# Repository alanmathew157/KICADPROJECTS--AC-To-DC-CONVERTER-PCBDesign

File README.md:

# AC to DC Converter PCB Design using KICAD -ALTIMUM
## PCB TOP VIEW

## PCB BOTTOM VIEW

## Project Overview
This project is an AC to DC converter circuit designed to convert alternating current (AC) input into a stable direct current (DC) output. The circuit uses a transformer to step down the input voltage, a bridge rectifier to convert AC to pulsating DC, and a filter capacitor to smooth the output. It demonstrates the basic principles of power supply design and provides a reliable DC source suitable for low-voltage electronic applications. This is my first KiCad project, created to learn schematic design and understand the fundamentals of circuit development

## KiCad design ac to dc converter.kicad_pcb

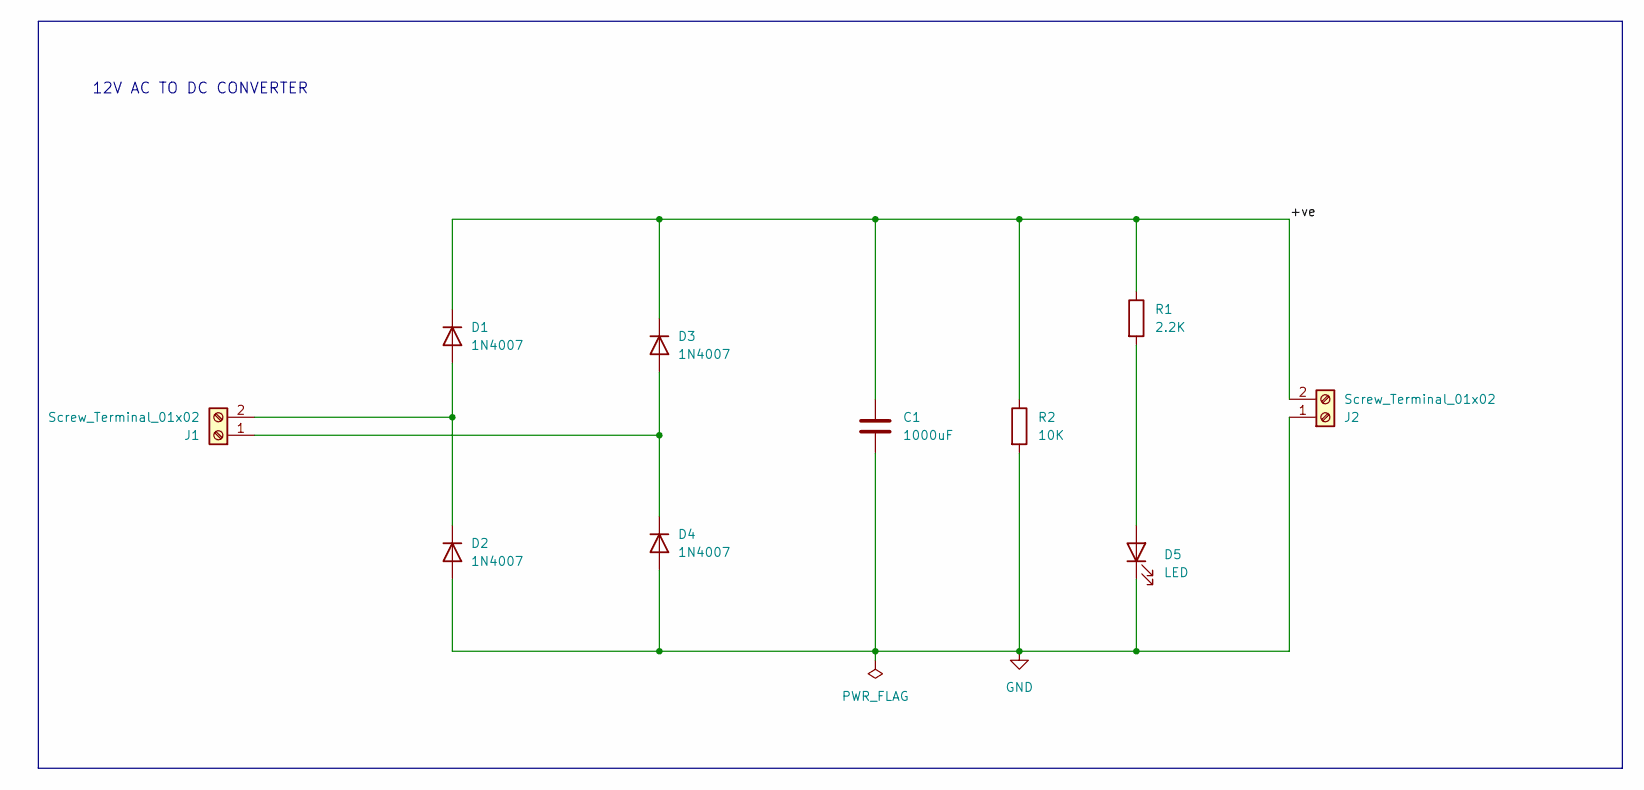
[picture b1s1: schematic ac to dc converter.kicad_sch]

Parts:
C1: 1000uF; C_Radial_D8.0mm_H11.5mm_P3.50mm
D1, D2, D3, D4: 1N4007; D_DO-41_SOD81_P10.16mm_Horizontal
D5: LED; LED_D5.0mm
J1, J2: Screw_Terminal_01x02; TerminalBlock_CUI_TB007-508-02_1x02_P5.08mm_Horizontal
R1: 2.2K; R_Axial_DIN0204_L3.6mm_D1.6mm_P7.62mm_Horizontal
R2: 10K; R_Axial_DIN0204_L3.6mm_D1.6mm_P7.62mm_Horizontal

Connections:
/+ve: C1.1, D1.1 (K), D3.1 (K), J2.2, R1.1, R2.1
GND: C1.2, D2.2 (A), D4.2 (A), D5.1 (K), J2.1, R2.2
unnamed: D1.2 (A), D2.1 (K), J1.2
unnamed: D3.2 (A), D4.1 (K), J1.1
unnamed: D5.2 (A), R1.2

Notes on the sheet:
12V AC TO DC CONVERTER

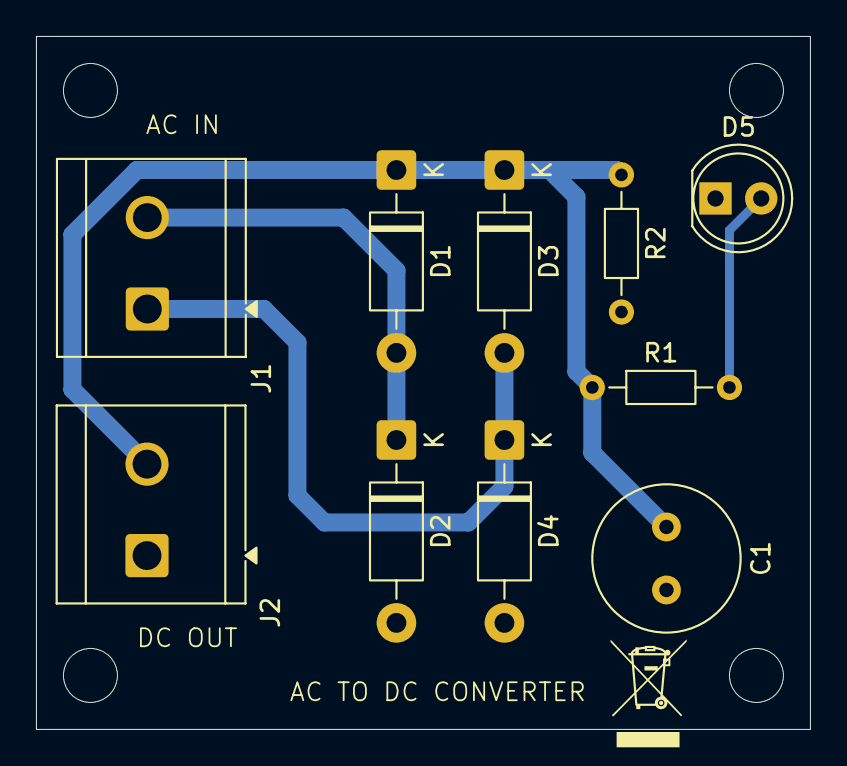
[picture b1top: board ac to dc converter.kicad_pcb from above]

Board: 2 copper layers, 43.0 x 38.5 mm, 10 parts (0 on the bottom side), 5 nets.

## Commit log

2026-03-01 Rename AC to DC BackSide.png to ACtoDCBackSide.png
2026-03-01 Rename ACtoDCBackSide.png to BackSide.png
2026-03-01 Fix image links for PCB top and bottom views
    Updated image references in README for PCB views.
